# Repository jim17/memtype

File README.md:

# Memtype
Open Source solution to store your passwords encrypted, having them available everywhere.

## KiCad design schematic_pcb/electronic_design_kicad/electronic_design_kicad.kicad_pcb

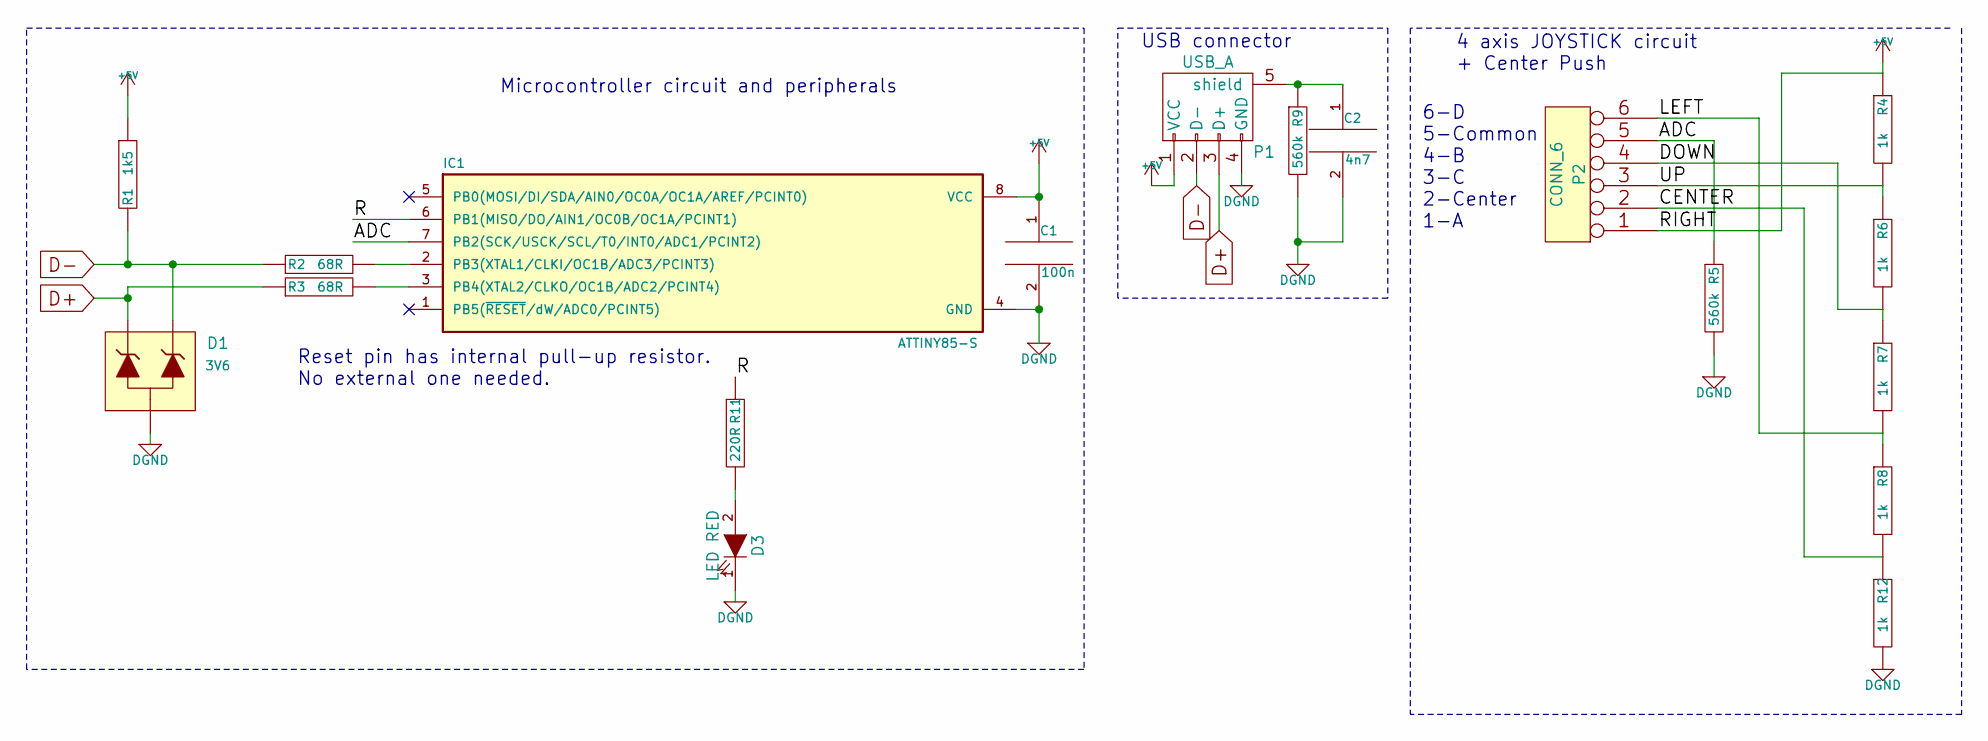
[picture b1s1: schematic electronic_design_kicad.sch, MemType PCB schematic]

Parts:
C1: 100n; SMD-0805; mouser C0805C104K5RACTU
C2: 4n7; SMD-0805; mouser C0805C472K5RACTU
D1: 3V6; SOT-23; mouser AZ23C3V6-E3-08
D3: LED RED; LED_0603_PIPE; mouser Q976-NR-1
IC1: ATTINY85-S; SO8_200mil_wide; mouser 556-ATTINY85-20SU
P1: USB_A; USB_A_MALE; mouser 534-932
P2: CONN_6; SKRHAAE010; mouser SKRHAAE010
R1: 1k5; SMD-0805; mouser ERJ-6GEYJ152V
R2, R3: 68R; SMD-0805; mouser ERJ-6GEYJ680V
R4, R6, R7, R8, R12: 1k; SMD-0805; mouser ERJ-6GEYJ102V
R5, R9: 560k; SMD-0805; mouser ERJ-6GEYJ564V
R11: 220R; SMD-0805; mouser ERJ-6GEYJ221V

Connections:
+5V: C1.1, IC1.8 (VCC), P1.1 (VCC), P2.1, R1.1, R4.1
/ADC: IC1.7 (PB2(SCK/USCK/SCL/T0/INT0/ADC1/PCINT2)), P2.5, R5.1
/CENTER: P2.2, R8.2, R12.1
/DOWN: P2.4, R6.2, R7.1
/LEFT: P2.6, R7.2, R8.1
/R: IC1.6 (PB1(MISO/DO/AIN1/OC0B/OC1A/PCINT1)), R11.1
/UP: P2.3, R4.2, R6.1
D+: D1.2 (K), P1.3 (D+), R3.1
D-: D1.1 (K), P1.2 (D-), R1.2, R2.1
DGND: C1.2, C2.2, D1.3 (A), D3.1 (K), IC1.4 (GND), P1.4 (GND), R5.2, R9.2, R12.2
unnamed: C2.1, P1.5 (shield), R9.1
unnamed: D3.2 (A), R11.2
unnamed: IC1.2 (PB3(XTAL1/CLKI/OC1B/ADC3/PCINT3)), R2.2
unnamed: IC1.3 (PB4(XTAL2/CLKO/OC1B/ADC2/PCINT4)), R3.2

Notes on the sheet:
4 axis JOYSTICK circuit + Center Push
USB connector
Microcontroller circuit and peripherals
6-D 5-Common 4-B 3-C 2-Center 1-A
Reset pin has internal pull-up resistor. No external one needed.

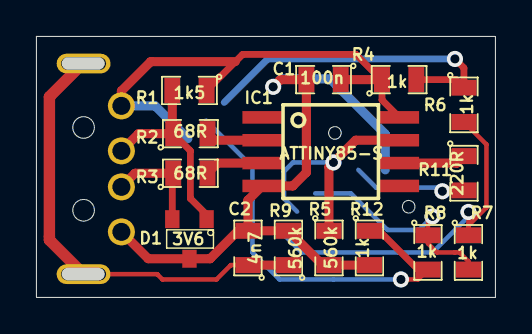
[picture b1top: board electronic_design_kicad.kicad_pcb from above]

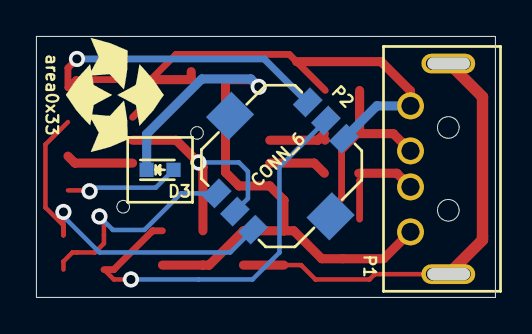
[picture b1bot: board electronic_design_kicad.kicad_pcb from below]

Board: 2 copper layers, 24.9 x 13.9 mm, 19 parts (4 on the bottom side), 14 nets.

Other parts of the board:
area0x33: LOGO; logo

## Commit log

2015-10-31 Version 3.0.0
2015-10-31 Added missing function prototypes that causes clang to error
2015-11-01 add CC-BY 4.0 License
2015-11-29 changed VID and PID to the one obtained in http://pid.codes/pids/
2015-12-04 updated mttool credential reading to support encrypted credentials also updated memtype Linux rules
2015-12-06 Added -static flag to Makefile so static binaries are generated when supported. Added bin directory with precompiled binaries
2015-12-06 Added first user manual version
2015-12-06 added windows bat file to compile mttool in windows
2015-12-06 revert back usbconfig and crd files
2015-12-09 added keyboard generation tool with custom memtype firmware
2015-12-09 added DE, EN, ES, FR, IT keyboards from keyboard branch
2015-12-11 User Manual to documentation folder
2015-12-11 Adding some windows hints to the user manual
2016-01-06 Solved MacOSX read bug
2016-01-06 Warnings cleanup
2016-01-19 first steps to memtype revision 2 pcb
2016-01-23 added first version files of mttool python scripts
2016-01-24 added info command
2016-01-25 credential List decrypt working after fixing endianess
2016-01-25 decryption of credentials working as expected
2016-01-25 added some comments to methods and functions
2016-01-26 memtype encryptCredentials function working as expected
2016-01-28 writing credentials done
2016-02-01 added 3d design files and finished schematic and PCB
2016-02-01 Clean old GUI code
2016-02-01 Clean uup the old memtype gui
2016-02-01 Added new GUI draft
2016-02-02 added gerber files for manufacture
2016-02-03 added more keyboard layouts
2016-02-06 changed internal RC calibration calibration routine, seems to fix bad behavior during enumeration in some USB with lot of bus activity
2016-02-06 add PDF plot of electronic design hardware rev2
2016-02-08 added make check for code formatting with uncrustify
2016-02-29 bumped firmware version to 3.1.0 according to Memtype hardware v2
2016-04-16 code refactor memtype and noekeon python tools
2016-04-16 added pinToKey python function to memtype library
2016-04-26 memtype hardware revision 2.1
2016-04-27 update joystick direction in schematic and code
2016-04-27 added travis script
2016-04-27 updated travis script
2016-05-01 modified UP/DOWN increment direction
2016-05-05 fix synchronous delay bug
2016-05-17 added DETAIL led blink feature
2016-06-09 clean up old mttool and GUI dirs
2016-06-19 hardware revision 3.0
2016-06-26 LOCK device after SET PIN command fix #1
2016-06-26 bumped to version 3.1.1 fix #1
2016-06-26 add Lock bits to Makefile and documentation
2016-06-27 updated getting started pdf
2016-07-12 updated Makefile and code with linking time optimization (lto)
2016-07-19 removed lto optimization
2016-07-19 fix #3 - Bumped to version 3.2.0, PIN hide pin numbers except the one being writted
2016-11-22 Added initial documentation WIP
2016-11-22 [Documentation] Added main benefeits of having passwords stored in password keeper
2016-11-23 Advancing a little bit more on the documentation
2016-11-23 Added more content to the documentation
2016-11-24 Filled the Quick Start on the documentation
2016-11-24 Filled the Credential section of the documentation
2016-11-28 Added some more information and screenshots to the documentation
2016-11-28 Changed images to links instead of embedded data-uri for faster loading in Documentation
2016-11-30 Added support for shaape diagrams under the diagrams directory. The make diagrams generates them
2016-11-30 No asciidoctor-diagram, instead diagrams are rendered to png and included as images in the .adoc file
2016-12-18 Changed 1ms task to 10ms to improve CPU load usage
2016-12-18 refactorized some files and rename of functions
2016-12-18 renaming of LED macros
2016-12-18 update to reduce code flash
2017-01-19 added 3 pin erroneous entries before reseting the pin back to 0000
2017-02-15 added BELGIAN keyboard layout generated with UBUNTU
2017-02-27 Windows Installers for PyQt4 were no more availables on the riverbank site, so we edited the link to the sourforge.net site. Also added a pdf version of the Documentation.
2017-10-14 Add files via upload
    Added Erase Pin and it's corresponding message.
2017-12-06 Update usi.c
    line 9: fixed pin retries to 3 instead of 4
    line 124: added erase pin routine
2017-12-12 Added Erase PIN and it's corresponding message (#19)
    * Update usi.c
    Added Erase Pin functionality
    line 9: Fixed pin retries to 3 instead of 4
2017-12-13 Added the MemType 3D case. Made by Yury MonZon.
2018-02-01 Added consistency between Schematic and Code
2018-02-12 Updated documentation to show new GUI installation in Linux, Windows and macOS.
2018-03-08 Improved changes to the documentation
2018-04-23 Workaround for KEY_EUROPE_2
2018-04-24 Workaround for KEY_EUROPE_2 (#23)
2024-02-02 Fixed the start value byte.
2024-02-02 Fixed the start value byte. (#26)
